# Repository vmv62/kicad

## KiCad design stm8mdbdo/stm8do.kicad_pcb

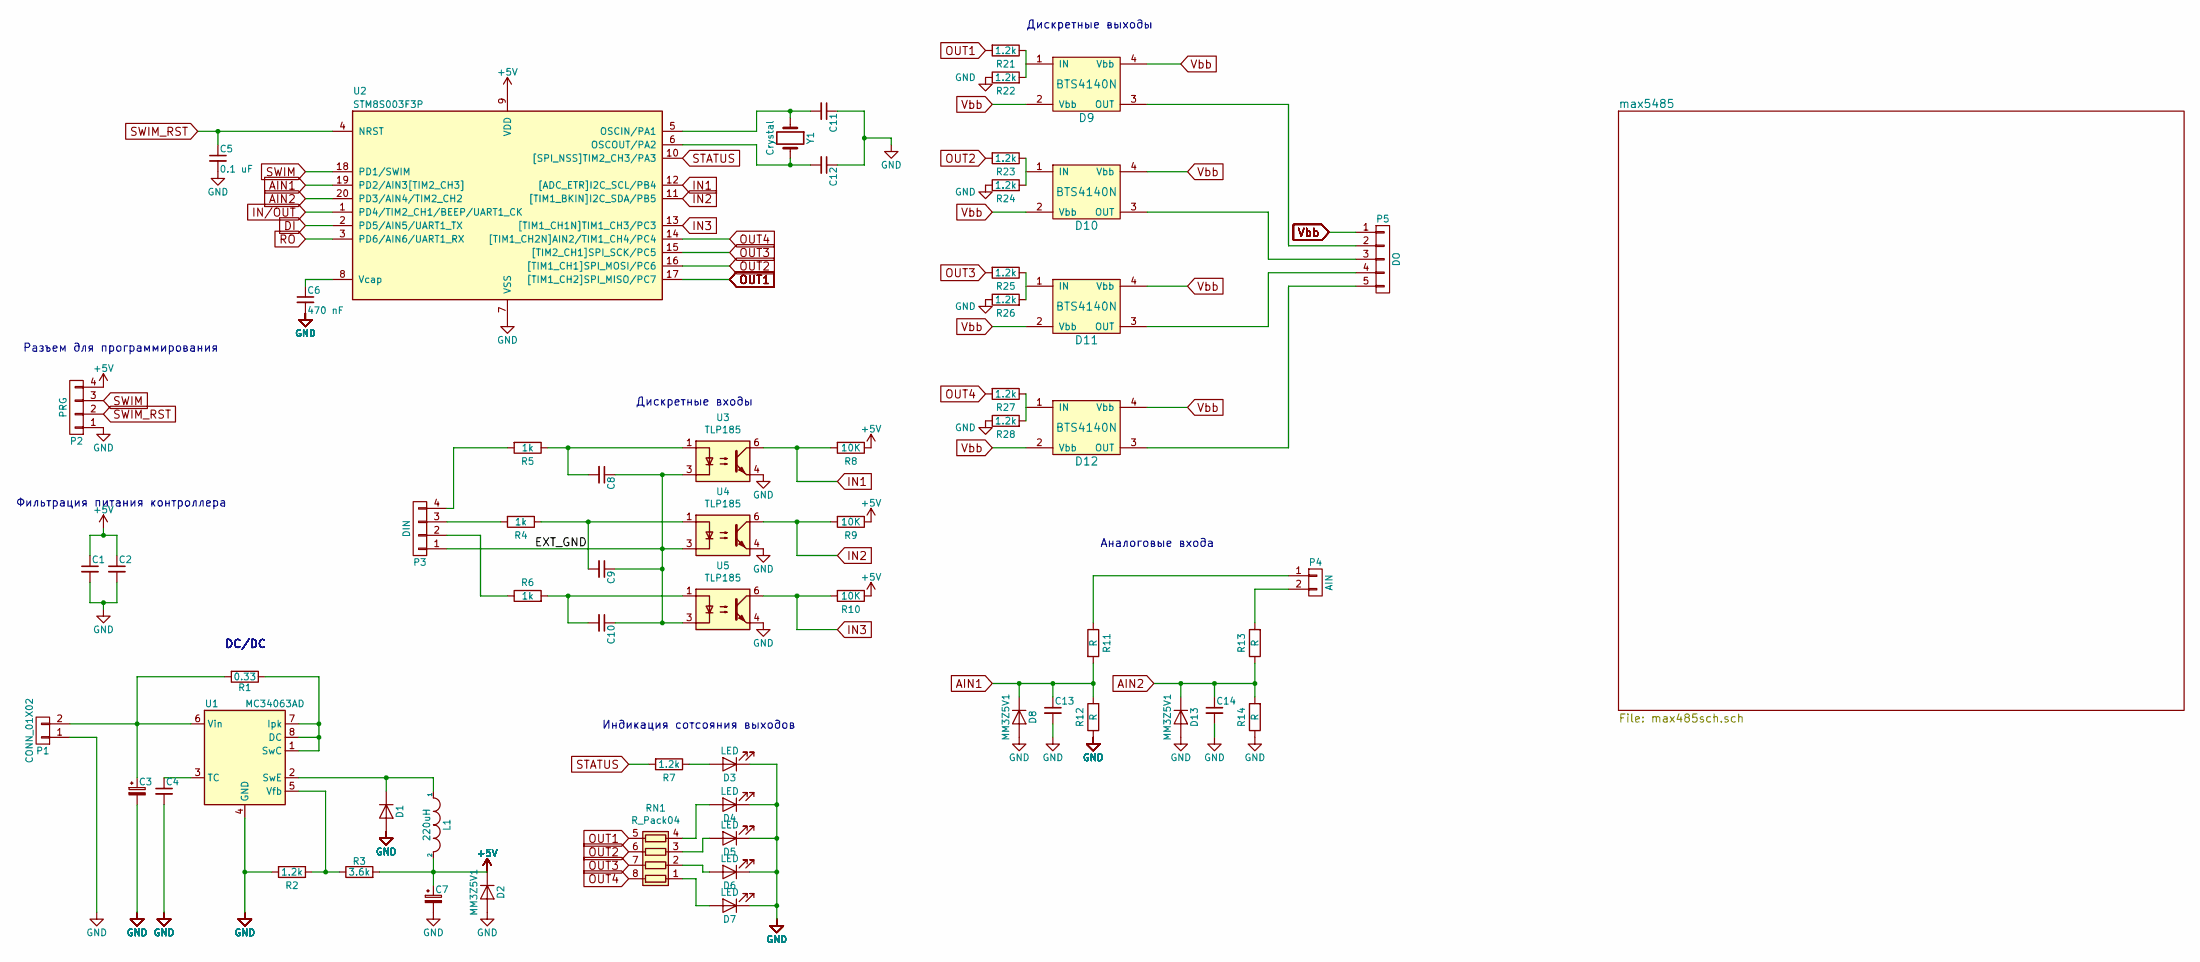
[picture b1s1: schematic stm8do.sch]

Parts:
C1, C2, C13, C14: C_Small; C_0805_2012Metric_Pad1.15x1.40mm_HandSolder
C3: 470uF; CP_Radial_D10.0mm_P5.00mm
C4, C8, C9, C10: 470pF; C_0805_2012Metric_Pad1.15x1.40mm_HandSolder
C5: 0.1 uF; C_0805_2012Metric_Pad1.15x1.40mm_HandSolder
C6: 470 nF; C_0805_2012Metric_Pad1.15x1.40mm_HandSolder
C7: 100uF; CP_Radial_D10.0mm_P5.00mm
C11, C12: 22pF; C_0805_2012Metric_Pad1.15x1.40mm_HandSolder
D1: SS36; D_SMC
D2: MM3Z5V1; D_0805_2012Metric_Pad1.15x1.40mm_HandSolder
D3, D4, D5, D6, D7: LED; LED_0805_2012Metric_Pad1.15x1.40mm_HandSolder
D8, D13: MM3Z5V1; D_0805_2012Metric
D9, D10, D11, D12: BTS4140N; SOT-223
L1: 220uH; L_2816_7142Metric_Pad3.20x4.45mm_HandSolder
P1: CONN_01X02; PinHeader_1x02_P1.27mm_Vertical_SMD_Pin1Left
P2: PRG; PinHeader_1x04_P1.27mm_Vertical
P3: DIN; PinHeader_1x04_P1.27mm_Horizontal
P4: AIN; TerminalBlock_bornier-3_P5.08mm
P5: DO; PinHeader_1x05_P1.27mm_Vertical
R1: 0.33; R_0805_2012Metric_Pad1.15x1.40mm_HandSolder
R2, R7, R21, R22, R23, R24, R25, R26, R27, R28: 1.2k; R_0805_2012Metric_Pad1.15x1.40mm_HandSolder
R3: 3.6k; R_0805_2012Metric_Pad1.15x1.40mm_HandSolder
R4, R5, R6: 1k; R_0805_2012Metric_Pad1.15x1.40mm_HandSolder
R8, R9, R10: 10K; R_0805_2012Metric_Pad1.15x1.40mm_HandSolder
R11, R12, R13, R14: R; R_0805_2012Metric_Pad1.15x1.40mm_HandSolder
RN1: R_Pack04; R_Array_Concave_4x0603
U1: MC34063AD; SOIC-8_3.9x4.9mm_P1.27mm
U2: STM8S003F3P; TSSOP-20_4.4x6.5mm_P0.65mm
U3, U4, U5: TLP185; SOIC-4_4.55x3.7mm_P2.54mm
Y1: Crystal; Crystal_SMD_HC49-SD_HandSoldering

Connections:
+5V: C1.1, C2.1, C7.1, D2.1 (K), L1.2, P2.4, R3.2, R8.1, R9.1, R10.1, U2.9 (VDD); also elsewhere on the board
/EXT_GND: C8.1, C9.1, C10.1, P3.1, U3.3, U4.3, U5.3
AIN1: C13.1, D8.1 (K), R11.2, R12.2, U2.19 (PD2/AIN3[TIM2_CH3])
AIN2: C14.1, D13.1 (K), R13.1, R14.2, U2.20 (PD3/AIN4/TIM2_CH2)
DI: U2.2 (PD5/AIN5/UART1_TX); also elsewhere on the board
GND: C1.2, C2.2, C3.2, C4.2, C5.2, C6.2, C7.2, C11.1, C12.1, C13.2, C14.2, D1.2 (A), D2.2 (A), D3.1 (K), D4.1 (K), D5.1 (K), D6.1 (K), D7.1 (K), D8.2 (A), D13.2 (A), P1.1, P2.1, R2.2, R12.1, R14.1, R22.1, R24.1, R26.1, R28.1, U1.4 (GND), U2.7 (VSS), U3.4, U4.4, U5.4; also elsewhere on the board
IN1: R8.2, U2.12 ([ADC_ETR]I2C_SCL/PB4), U3.6
IN2: R9.2, U2.11 ([TIM1_BKIN]I2C_SDA/PB5), U4.6
IN3: R10.2, U2.13 ([TIM1_CH1N]TIM1_CH3/PC3), U5.6
IN/OUT: U2.1 (PD4/TIM2_CH1/BEEP/UART1_CK); also elsewhere on the board
unnamed: C3.1, P1.2, R1.2, U1.6 (Vin)
unnamed: C4.1, U1.3 (TC)
unnamed: C6.1, U2.8 (Vcap)
unnamed: C8.2, R5.1, U3.1
unnamed: C9.2, R4.1, U4.1
unnamed: C10.2, R6.2, U5.1
unnamed: C11.2, U2.5 (OSCIN/PA1), Y1.1
unnamed: C12.2, U2.6 (OSCOUT/PA2), Y1.2
unnamed: D1.1 (K), L1.1, U1.2 (SwE)
unnamed: D3.2 (A), R7.1
unnamed: D4.2 (A), RN1.4 (R4.1)
unnamed: D5.2 (A), RN1.3 (R3.1)
unnamed: D6.2 (A), RN1.2 (R2.1)
unnamed: D7.2 (A), RN1.1 (R1.1)
unnamed: D9.3 (OUT), P5.2
unnamed: D10.3 (OUT), P5.3
unnamed: D11.3 (OUT), P5.4
unnamed: D12.3 (OUT), P5.5
unnamed: P3.2, R6.1
unnamed: P3.3, R4.2
unnamed: P3.4, R5.2
unnamed: P4.1, R11.1
unnamed: P4.2, R13.2
unnamed: R1.1, U1.1 (SwC), U1.7 (Ipk), U1.8 (DC)
unnamed: R2.1, R3.1, U1.5 (Vfb)
unnamed: R21.1, R22.2
unnamed: R23.1, R24.2
unnamed: R25.1, R26.2
unnamed: R27.1, R28.2
OUT1: R21.2, RN1.5 (R4.2), U2.17 ([TIM1_CH2]SPI_MISO/PC7)
OUT2: R23.2, RN1.6 (R3.2), U2.16 ([TIM1_CH1]SPI_MOSI/PC6)
OUT3: R25.2, RN1.7 (R2.2), U2.15 ([TIM2_CH1]SPI_SCK/PC5)
OUT4: R27.2, RN1.8 (R1.2), U2.14 ([TIM1_CH2N]AIN2/TIM1_CH4/PC4)
RO: U2.3 (PD6/AIN6/UART1_RX); also elsewhere on the board
STATUS: R7.2, U2.10 ([SPI_NSS]TIM2_CH3/PA3)
SWIM: P2.3, U2.18 (PD1/SWIM)
SWIM_RST: C5.1, P2.2, U2.4 (NRST)
Vbb: D9.2 (Vbb), D9.4 (Vbb), D10.2 (Vbb), D10.4 (Vbb), D11.2 (Vbb), D11.4 (Vbb), D12.2 (Vbb), D12.4 (Vbb), P5.1

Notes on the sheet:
DC/DC
Индикация сотсояния выходов
Дискретные выходы
Дискретные входы
Фильтрация питания контроллера
Аналоговые входа
Разъем для программирования

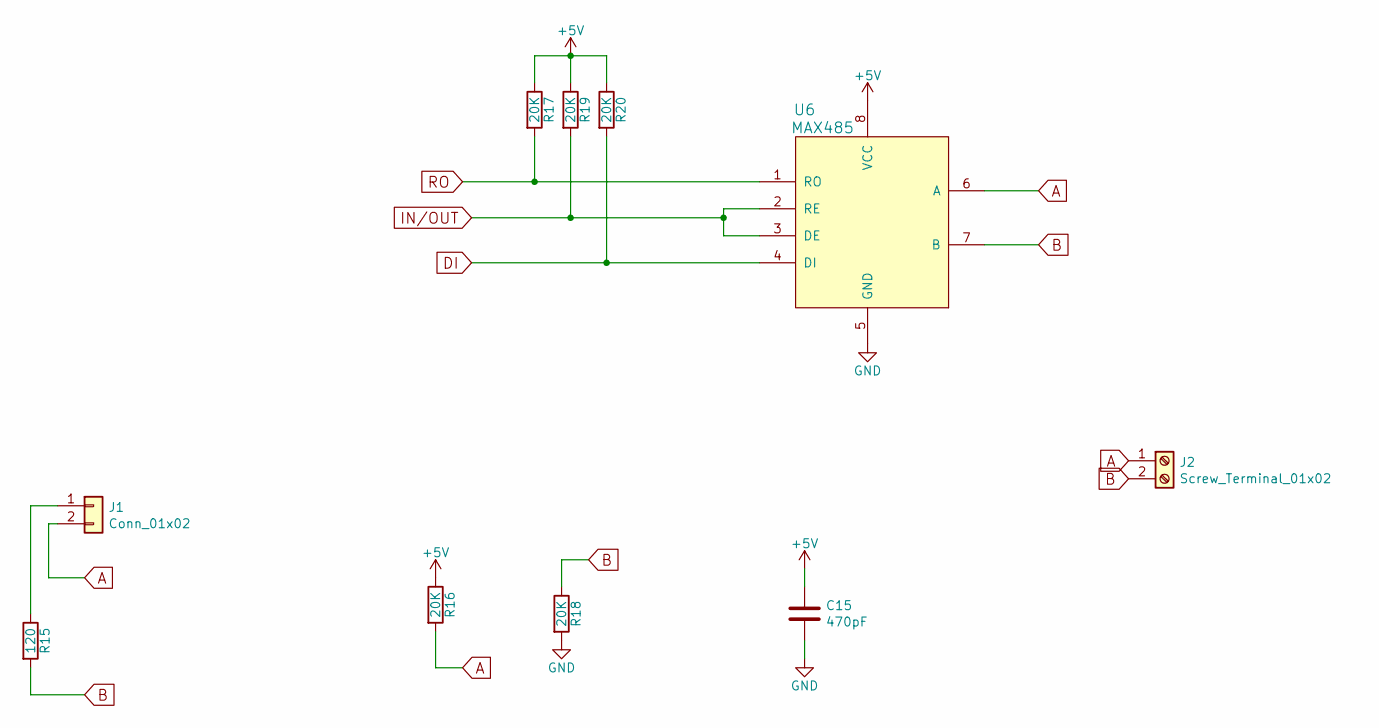
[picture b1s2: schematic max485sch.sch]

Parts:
C15: 470pF; C_0805_2012Metric_Pad1.15x1.40mm_HandSolder
J1: Conn_01x02; PinHeader_1x02_P1.27mm_Vertical
J2: Screw_Terminal_01x02; TerminalBlock_bornier-2_P5.08mm
R15: 120; R_0805_2012Metric_Pad1.15x1.40mm_HandSolder
R16, R17, R18, R19, R20: 20K; R_0805_2012Metric_Pad1.15x1.40mm_HandSolder
U6: MAX485; SOIC-8_3.9x4.9mm_P1.27mm

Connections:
+5V: C15.1, R16.1, R17.1, R19.1, R20.1, U6.8 (VCC); also elsewhere on the board
A+: J1.2, J2.1, R16.2, U6.6 (A)
B-: J2.2, R15.2, R18.1, U6.7 (B)
DI: R20.2, U6.4 (DI); also elsewhere on the board
GND: C15.2, R18.2, U6.5 (GND); also elsewhere on the board
IN/OUT: R19.2, U6.2 (RE), U6.3 (DE); also elsewhere on the board
unnamed: J1.1, R15.1
RO: R17.2, U6.1 (RO); also elsewhere on the board

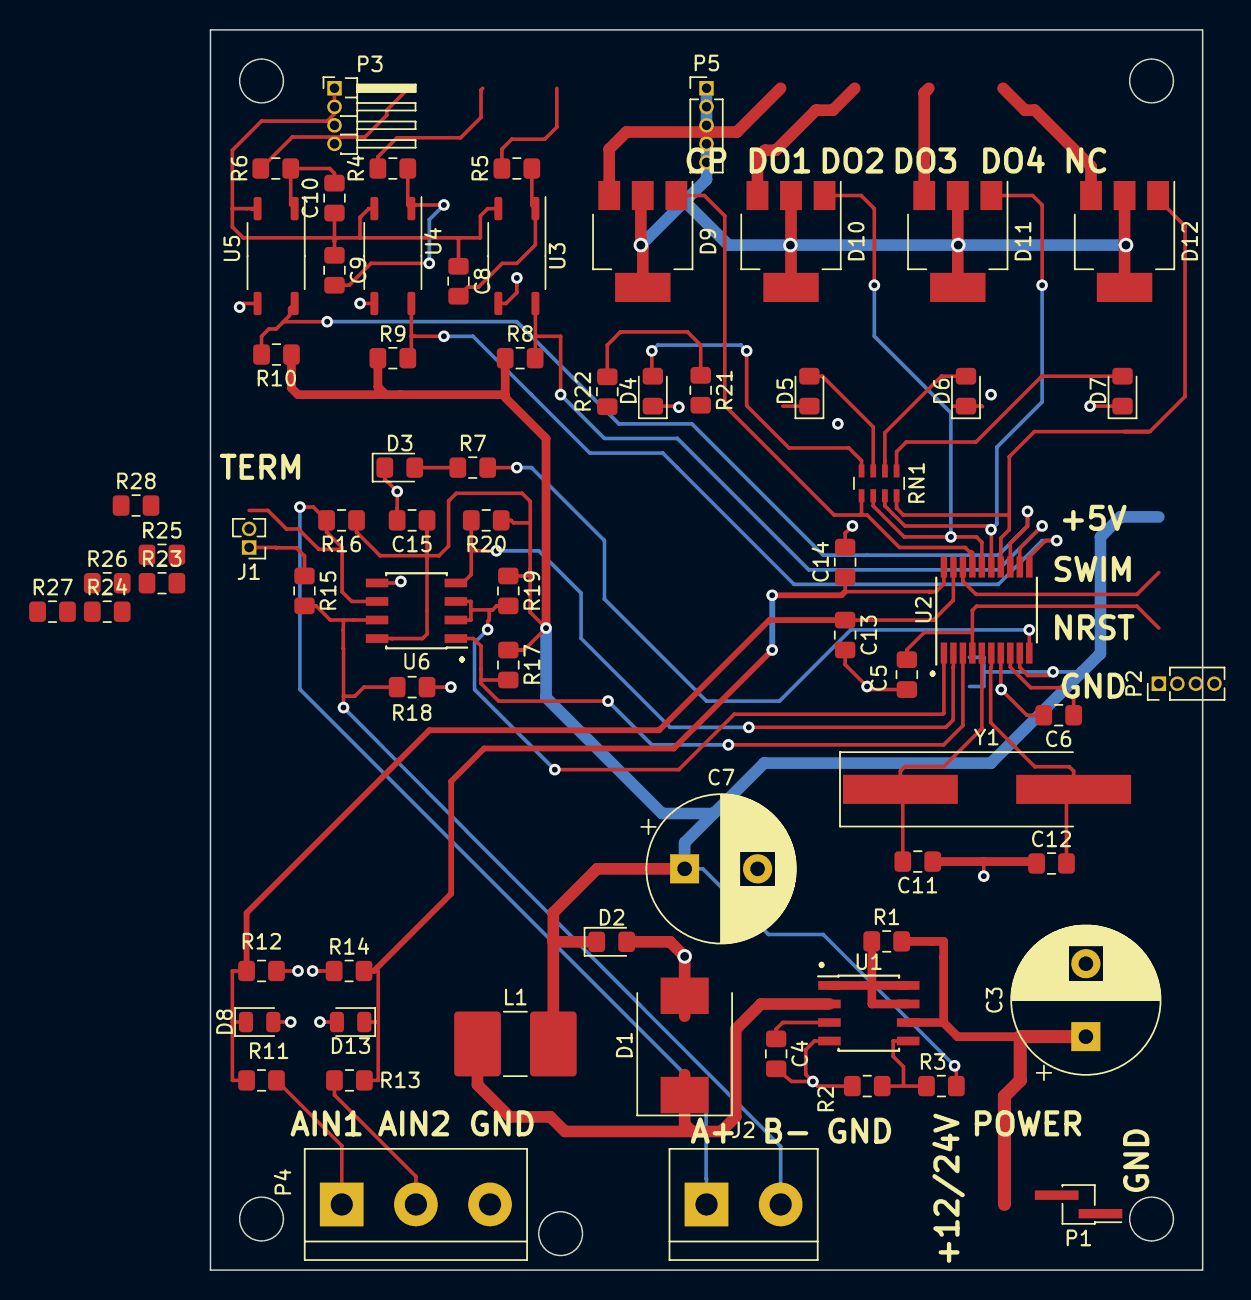
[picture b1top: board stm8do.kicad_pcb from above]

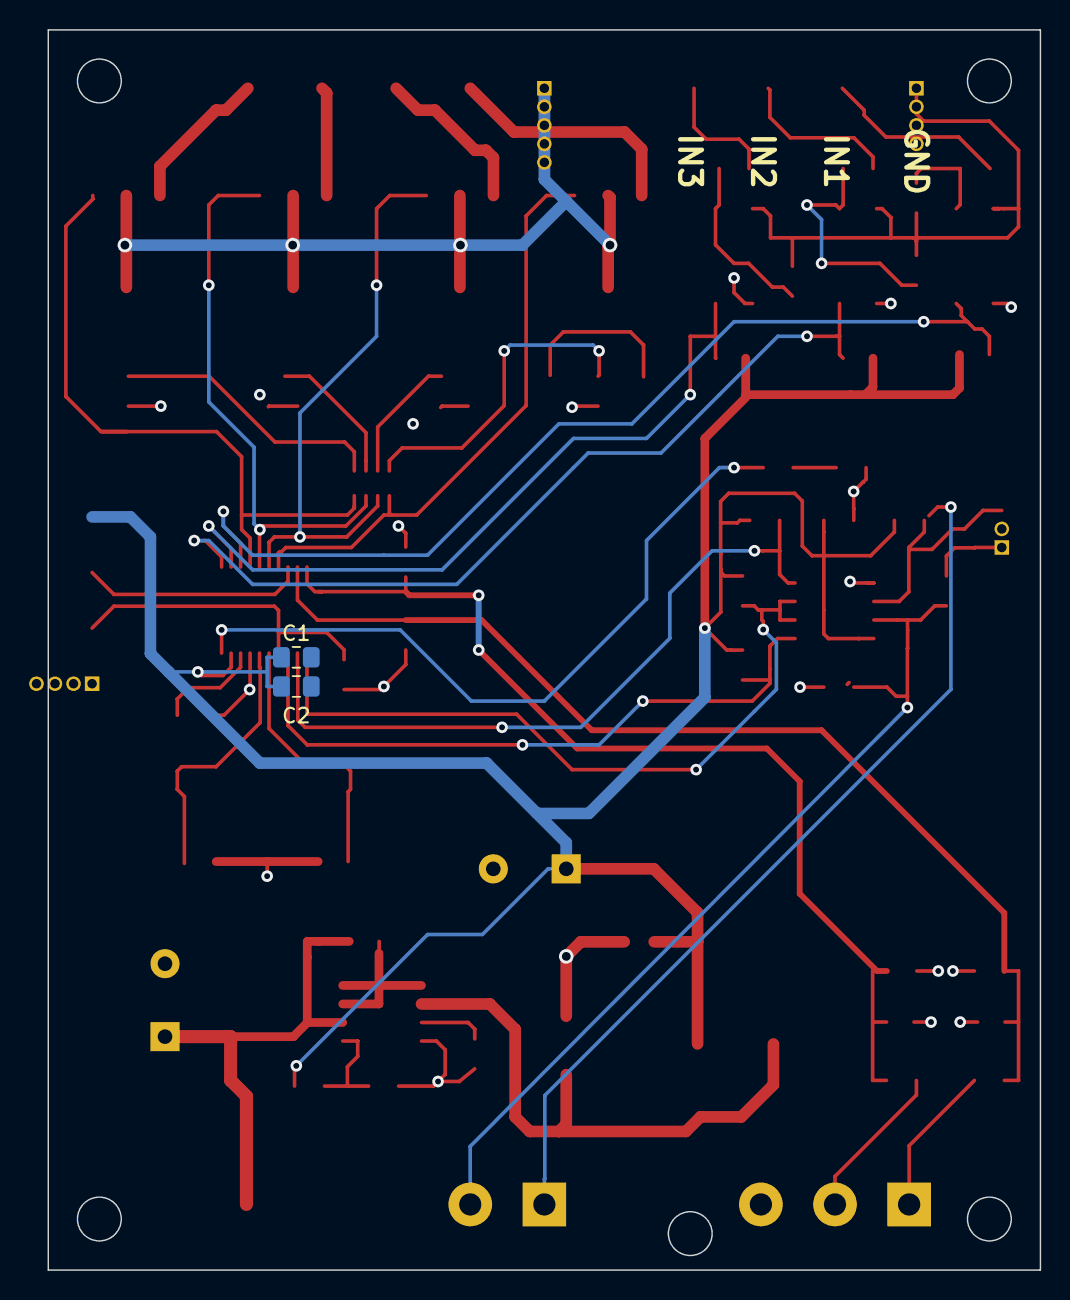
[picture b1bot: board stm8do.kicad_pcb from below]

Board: 2 copper layers, 68.0 x 85.0 mm, 72 parts (2 on the bottom side), 51 nets.

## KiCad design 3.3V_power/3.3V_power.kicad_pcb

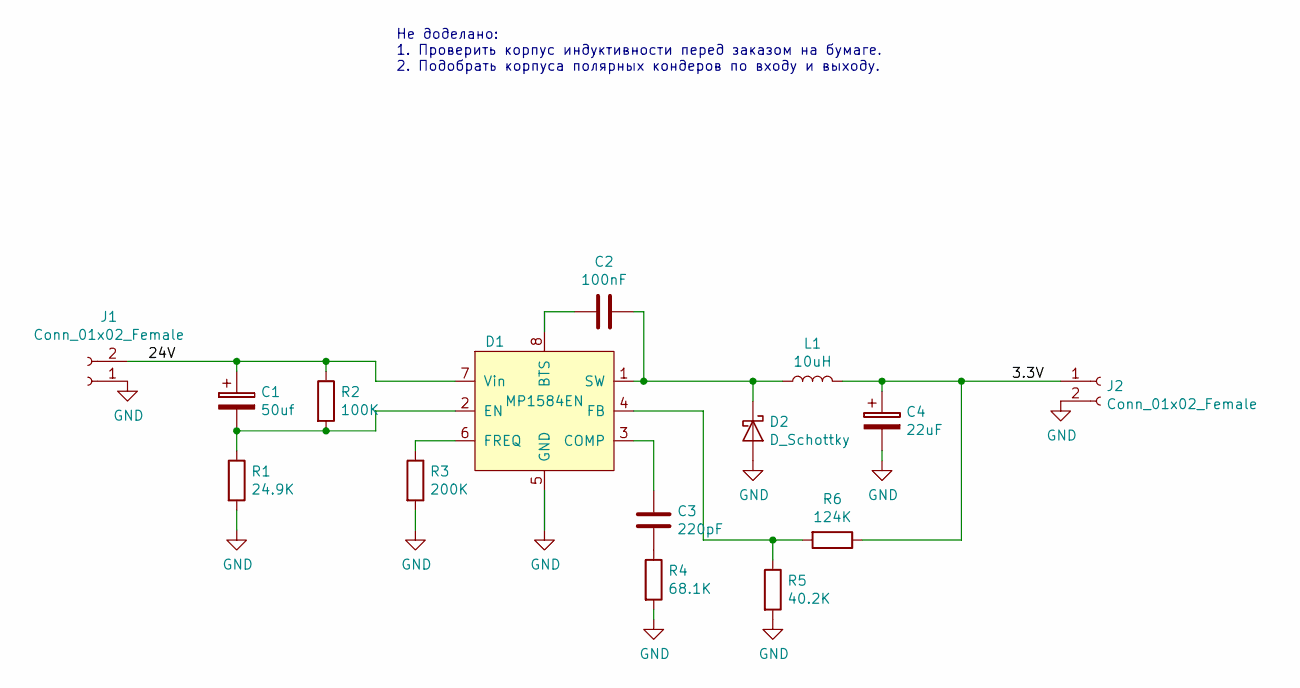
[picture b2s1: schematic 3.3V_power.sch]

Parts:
C1: 50uf; CP_EIA-7343-43_Kemet-X_Pad2.25x2.55mm_HandSolder
C2: 100nF; C_0805_2012Metric_Pad1.15x1.40mm_HandSolder
C3: 220pF; C_0805_2012Metric_Pad1.15x1.40mm_HandSolder
C4: 22uF; CP_EIA-7343-43_Kemet-X_Pad2.25x2.55mm_HandSolder
D1: MP1584EN; HTSOP-8-1EP_3.9x4.9mm_P1.27mm_EP2.4x3.2mm_ThermalVias
D2: D_Schottky; D_0603_1608Metric_Pad1.05x0.95mm_HandSolder
J1: Conn_01x02_Female; SolderWirePad_1x02_P5.08mm_Drill1.5mm
J2: Conn_01x02_Female; PinHeader_1x02_P1.27mm_Vertical
L1: 10uH; L_Wuerth_WE-PD2-Typ-MS
R1: 24.9K; R_0805_2012Metric_Pad1.15x1.40mm_HandSolder
R2: 100K; R_0805_2012Metric_Pad1.15x1.40mm_HandSolder
R3: 200K; R_0805_2012Metric_Pad1.15x1.40mm_HandSolder
R4: 68.1K; R_0805_2012Metric_Pad1.15x1.40mm_HandSolder
R5: 40.2K; R_0805_2012Metric_Pad1.15x1.40mm_HandSolder
R6: 124K; R_0805_2012Metric_Pad1.15x1.40mm_HandSolder

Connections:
/3.3V: C4.1, J2.1, L1.2, R6.1
/24V: C1.1, D1.7 (Vin), J1.2, R2.1
GND: C4.2, D1.5 (GND), D2.2 (A), J1.1, J2.2, R1.2, R3.2, R4.2, R5.2
unnamed: C1.2, D1.2 (EN), R1.1, R2.2
unnamed: C2.1, D1.1 (SW), D2.1 (K), L1.1
unnamed: C2.2, D1.8 (BTS)
unnamed: C3.1, R4.1
unnamed: C3.2, D1.3 (COMP)
unnamed: D1.4 (FB), R5.1, R6.2
unnamed: D1.6 (FREQ), R3.1

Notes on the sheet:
Не доделано: 1. Проверить корпус индуктивности перед заказом на бумаге. 2. Подобрать корпуса полярных кондеров по входу и выходу.

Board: 2 copper layers, 15 parts (0 on the bottom side), 10 nets, no tracks yet.

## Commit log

2019-02-17 Готова схема. Проверить все посадочные места, уточнить схему входов, выходов.
2019-02-28 Решена проблемма с библиотекой для конденсаторов. Просто сделал копию папки с именем которое содержится в ошибке.
2019-03-01 Перевод на новую библиотеку со спасением старых
2019-03-01 Auto
2019-03-01 Auto commit date
2019-03-01 Auto commit
2019-03-01 Auto commit $date
2020-04-24 Added some chems
2020-04-24 Added some chematics
